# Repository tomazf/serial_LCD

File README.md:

# serial_LCD
display incoming serial data on LCD (ie. 16x2, 20x4)

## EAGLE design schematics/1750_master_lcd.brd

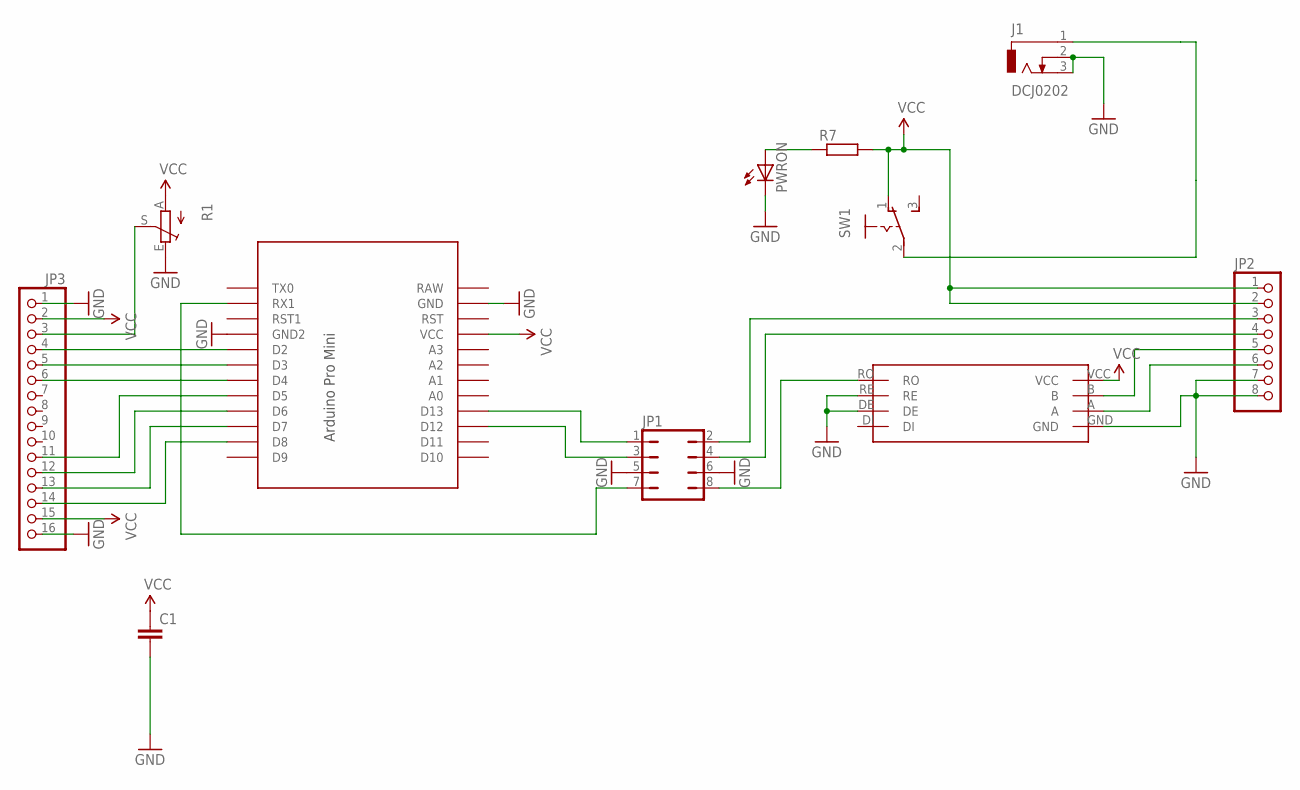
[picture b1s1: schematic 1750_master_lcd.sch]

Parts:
C1: C-EU025-025X050; C025-025X050
J1: DCJ0202
JP1: JP4Q
JP2: PINHD-1X8; 1X08
JP3: PINHD-1X16; 1X16
PWRON: LED5MM
R1: TRIM_EU-CA6V; CA6V
R7: R-EU_0207/10; 0207/10
SW1: 255SB
U$2: 485F
U$3: PRO-MINI-F

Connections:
GND: C1.2, J1.2, J1.3, JP1.5, JP1.6, JP2.7, JP2.8, JP3.1, JP3.16, PWRON.K (C), R1.E, U$2.DE, U$2.GND, U$2.RE, U$3.GND, U$3.GND1 (GND2)
unnamed: JP2.5, U$2.B
unnamed: JP2.6, U$2.A
unnamed: JP1.4, JP2.4
unnamed: JP1.2, JP2.3
unnamed: J1.1, SW1.2
unnamed: JP1.8, U$2.RO
unnamed: JP1.7, U$3.RX1
unnamed: JP1.1, U$3.D13
unnamed: JP1.3, U$3.D12
unnamed: JP3.3, R1.S
unnamed: JP3.4, U$3.D2
unnamed: JP3.5, U$3.D3
unnamed: JP3.6, U$3.D4
unnamed: JP3.11, U$3.D5
unnamed: JP3.12, U$3.D6
unnamed: JP3.13, U$3.D7
unnamed: JP3.14, U$3.D8
unnamed: PWRON.A, R7.1
VCC: C1.1, JP2.1, JP2.2, JP3.2, JP3.15, R1.A, R7.2, SW1.1 (O), U$2.VCC, U$3.VCC

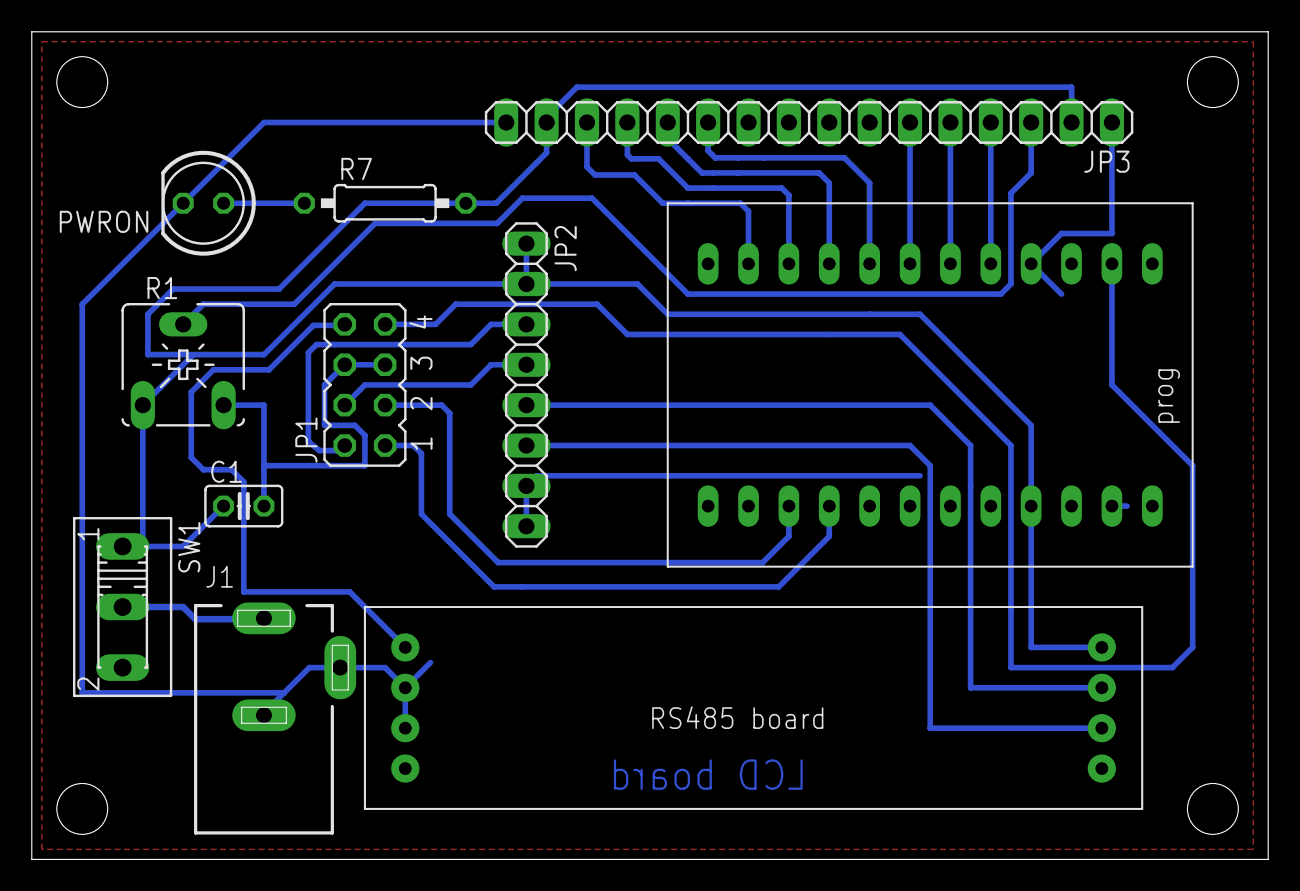
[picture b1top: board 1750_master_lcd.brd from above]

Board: 2 copper layers, 77.8 x 52.1 mm, 11 parts (0 on the bottom side), 20 nets.

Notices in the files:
parts and their libraries:
SparkFun-Aesthetics: Licensing: Creative Commons ShareAlike 4.0 International - https://creativecommons.org/licenses/by-sa/4.0
